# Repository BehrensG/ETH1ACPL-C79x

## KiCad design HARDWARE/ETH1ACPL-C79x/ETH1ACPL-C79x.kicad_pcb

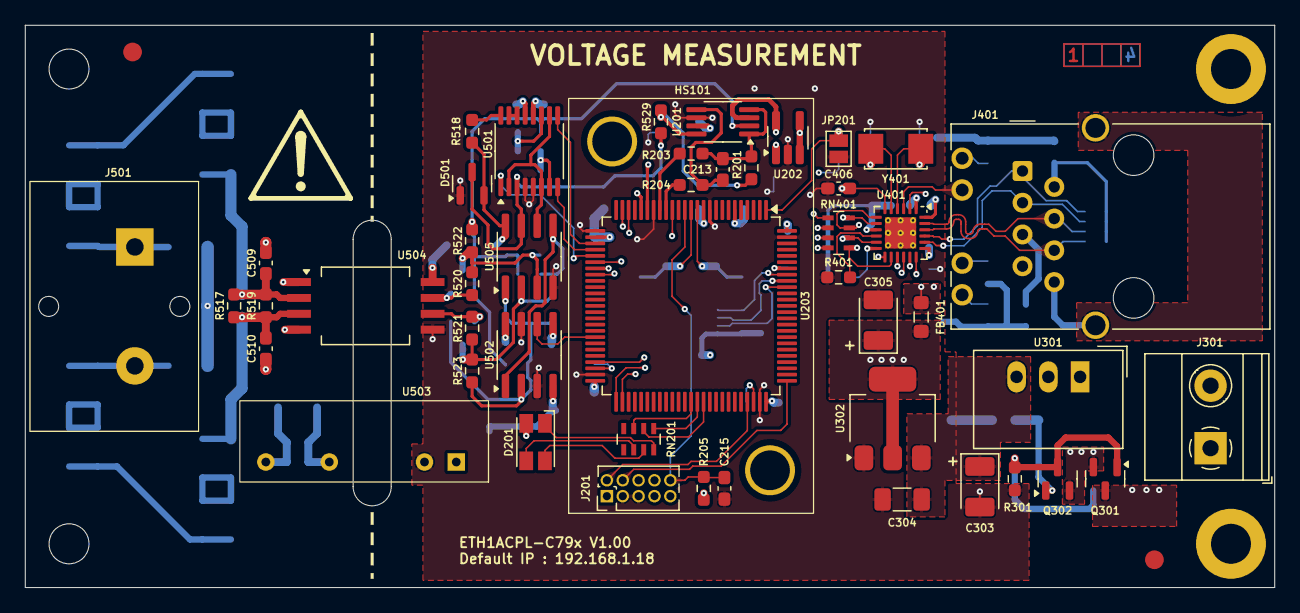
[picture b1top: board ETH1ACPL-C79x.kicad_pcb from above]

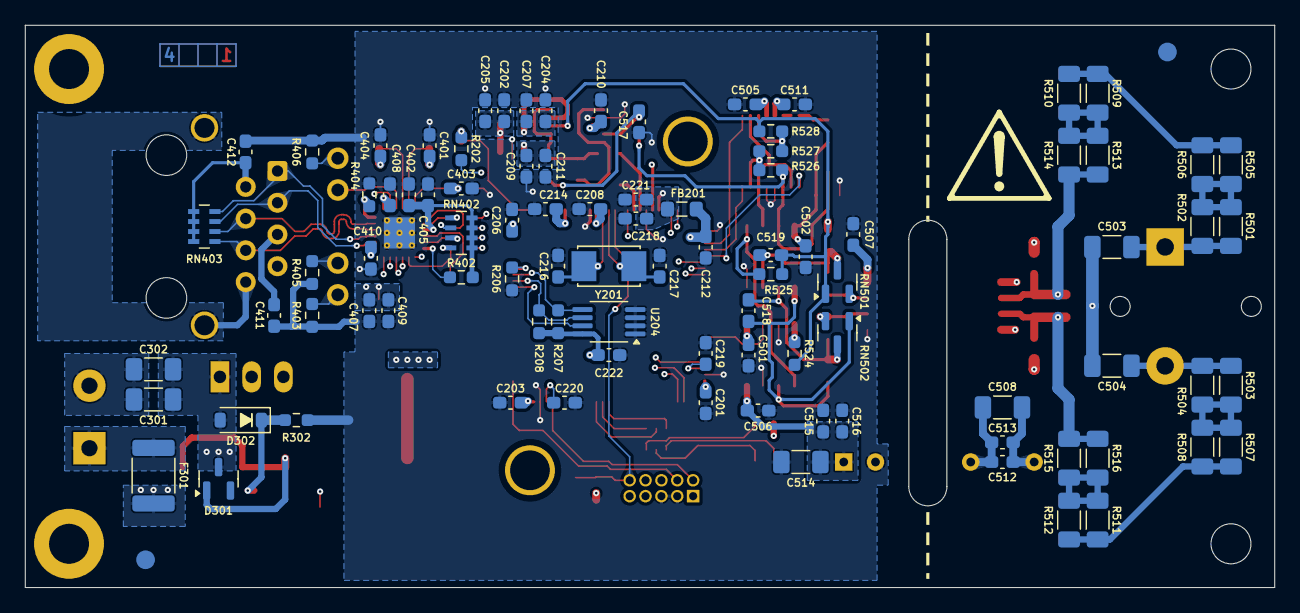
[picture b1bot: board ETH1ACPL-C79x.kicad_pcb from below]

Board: 4 copper layers, 100.0 x 45.0 mm, 148 parts (94 on the bottom side), 91 nets.

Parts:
C201, C203, C204, C205, C206, C208, C209, C210, C212, C215, C221, C222, C402, C408, C409, C410, C411, C412, C501, C502, C505, C506, C507, C511, C513, C516: 0.1u; C_0603_1608Metric_Pad1.08x0.95mm_HandSolder
C202, C207, C211, C214, C218, C405, C406, C407, C512, C515: 1u; C_0603_1608Metric_Pad1.08x0.95mm_HandSolder
C213: DNP; C_0603_1608Metric_Pad1.08x0.95mm_HandSolder
C216, C217, C401, C404: 8p; C_0603_1608Metric_Pad1.08x0.95mm_HandSolder
C219, C220: 2u2; C_0603_1608Metric_Pad1.08x0.95mm_HandSolder
C301: 10u/50V; C_1206_3216Metric_Pad1.33x1.80mm_HandSolder
C302: 4u7/50V; C_1206_3216Metric_Pad1.33x1.80mm_HandSolder
C303, C305: 22u; CP_EIA-3528-21_Kemet-B_Pad1.50x2.35mm_HandSolder
C304, C508, C514: 10u; C_1206_3216Metric_Pad1.33x1.80mm_HandSolder
C403: 470p; C_0603_1608Metric_Pad1.08x0.95mm_HandSolder
C503, C504: 1n/2kV; C_1206_3216Metric_Pad1.33x1.80mm_HandSolder
C509, C510: 470n/100; C_0603_1608Metric_Pad1.08x0.95mm_HandSolder
C517: 100p; C_0603_1608Metric_Pad1.08x0.95mm_HandSolder
C518, C519: 68p; C_0603_1608Metric_Pad1.08x0.95mm_HandSolder
D201: ASMB-MTB1-0B3A2; LED_Avago_PLCC4_3.2x2.8mm_CW
D301: BZX84C10LT1G; SOT-23
D302: 1N4148W; D_SOD-123
D501: BAV99; SOT-23
F301: 1812L075/33DR; Fuse_1812_4532Metric_Pad1.30x3.40mm_HandSolder
FB201, FB401: 742792031; L_0805_2012Metric_Pad1.05x1.20mm_HandSolder
FID101, FID102, FID103, FID104: Fiducial; Fiducial_1.5mm_Mask3mm
H101, H103: M3; MountingHole_3.2mm_M3_DIN965
H102, H104: M3; MountingHole_3.2mm_M3_DIN965_Pad
HS101: 960-19-12-S-AB-0
J201: 20021111-00010T4LF; PinHeader_2x05_P1.27mm_Vertical
J301: 1715721; TerminalBlock_Phoenix_MKDS-1,5-2_1x02_P5.00mm_Horizontal
J401: RJ45_Wuerth_7499010121A; RJ45_Wuerth_7499010121A_Horizontal
J501: 1710072
JP201: Open; SolderJumper-2_P1.3mm_Open_Pad1.0x1.5mm
Q301: SI5618A; SOT-23
Q302: MMBT3904; SOT-23
R201, R203, R204, R206, R524, R529: 0; R_0603_1608Metric_Pad0.98x0.95mm_HandSolder
R202, R205, R401, R403: 10k; R_0603_1608Metric_Pad0.98x0.95mm_HandSolder
R207, R208: 4k7; R_0603_1608Metric_Pad0.98x0.95mm_HandSolder
R301, R302, R518: 100k; R_0603_1608Metric_Pad0.98x0.95mm_HandSolder
R402: 1k5; R_0603_1608Metric_Pad0.98x0.95mm_HandSolder
R404: 12k1; R_0603_1608Metric_Pad0.98x0.95mm_HandSolder
R405, R406: 560; R_0603_1608Metric_Pad0.98x0.95mm_HandSolder
R501, R502, R503, R504, R505, R506, R507, R508, R509, R510, R511, R512, R513, R514, R515, R516: 56k; R_1206_3216Metric_Pad1.30x1.75mm_HandSolder
R517: 56; R_0603_1608Metric_Pad0.98x0.95mm_HandSolder
R519: 220; R_0603_1608Metric_Pad0.98x0.95mm_HandSolder
R520, R521: 10k/0.1%; R_0603_1608Metric_Pad0.98x0.95mm_HandSolder
R522, R523: 6k2/0.1%; R_0603_1608Metric_Pad0.98x0.95mm_HandSolder
R525: 100k/0.1%; R_0603_1608Metric_Pad0.98x0.95mm_HandSolder
R526: 180k/0.05%; R_0603_1608Metric_Pad0.98x0.95mm_HandSolder
R527: 18k/0.05%; R_0603_1608Metric_Pad0.98x0.95mm_HandSolder
R528: 2k/0.05%; R_0603_1608Metric_Pad0.98x0.95mm_HandSolder
RN201: EXB-V8V102JV; R_Array_Concave_4x0603
RN401: EXB-V8V330JV; R_Array_Concave_4x0603
RN402: EXB-V8V103JV; R_Array_Concave_4x0603
RN403: EXB-38V510JV; R_Array_Concave_4x0603
RN501, RN502: MPMT50011002AT5; SOT-23
SYM501, SYM502: SYM_Flash_Small; Symbol_Attention_Triangle_8x7mm_Copper
U201: LT6350xMS8; MSOP-8_3x3mm_P0.65mm
U202: REF1933AIDDCT; SOT-23-5_HandSoldering
U203: STM32H743VITx; LQFP-100_14x14mm_P0.5mm
U204: 24LC08B-E/MS; MSOP-8_3x3mm_P0.65mm
U301: TSR_1-2450; Converter_DCDC_TRACO_TSR-1_THT
U302: LM1117MP-3.3/NOPB; SOT-223-3_TabPin2
U401: LAN8742A; VQFN-24-1EP_4x4mm_P0.5mm_EP2.5x2.5mm_ThermalVias
U501: DG412LEDQ; TSSOP-16_4.4x5mm_P0.65mm
U502: DG419LEDY; SOIC-8_3.9x4.9mm_P1.27mm
U503: TBA 1-0511HI; TBA1
U504: ACPL-C79B; SSO-8_6.8x5.9mm_P1.27mm_Clearance8mm
U505: OPA2340UA; SOIC-8_3.9x4.9mm_P1.27mm
Y201: NX5032GA-16; NX5032GA
Y401: NX5032GA-25; NX5032GA

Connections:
+1.65V: C209.1, C211.1, C519.2, R522.1, R524.2, R525.2, R528.2, RN501.1, U201.2 (+IN2), U202.1 (Vbias)
+3.3V: C201.1, C203.1, C206.1, C208.1, C212.1, C214.1, C222.2, C305.1, C402.1, C405.1, C501.1, C502.1, C505.1, D201.4 (A), D501.2 (A), FB201.2, FB401.2, J201.1, R202.2, R205.1, R207.1, R208.1, R402.1, R518.2, RN402.5 (R4.2), RN402.6 (R3.2), RN402.7 (R2.2), RN402.8 (R1.2), U203.6 (VBAT), U203.11 (VDD), U203.27 (VDD), U203.50 (VDD), U203.75 (VDD), U203.100 (VDD), U204.8 (VCC), U302.2 (VO), U401.9 (VDDIO), U501.12 (VL), U502.5 (VL), U505.8 (V+)
+3.3VADC: C204.1, C207.1, C210.1, U201.3 (V+), U201.7 (~SHDN), U202.5 (Vref), U203.20 (VREF+)
+5V: C202.1, C205.1, C303.1, C304.1, C506.1, C507.1, C511.1, C514.1, C515.1, C516.1, U202.3 (EN), U202.4 (Vin), U301.3 (Vout), U302.3 (VI), U501.13 (V+), U502.4 (V+), U503.1 (+Vin), U504.8 (VDD2)
+5VP: C508.1, C512.1, C513.1, U503.6 (+Vout), U504.1 (VDD1)
/Ethernet/ETH_RXN: J401.6 (RD-), RN403.1 (R1.1), U401.22 (RXN)
/Ethernet/ETH_RXP: J401.4 (RD+), RN403.2 (R2.1), U401.23 (RXP)
/Ethernet/ETH_TXN: J401.3 (TD-), RN403.3 (R3.1), U401.20 (TXN)
/Ethernet/ETH_TXP: J401.1 (TD+), RN403.4 (R4.1), U401.21 (TXP)
/Ethernet/LED1: J401.10, U401.3 (LED1/REGOFF)
/Ethernet/LED2: J401.12, R403.1, U401.2 (LED2/~INTSEL)
/Ethernet/MODE0: RN401.8 (R1.2), RN402.1 (R1.1), U401.8 (RXD0/MODE0)
/Ethernet/MODE1: RN401.7 (R2.2), RN402.2 (R2.1), U401.7 (RXD1/MODE1)
/Ethernet/MODE2: RN401.6 (R3.2), RN402.3 (R3.1), U401.11 (CRS_DV/MODE2)
/Ethernet/REFCLK0: RN401.5 (R4.2), RN402.4 (R4.1), U401.14 (~INT/REFCLKO)
/Ethernet/REF_CLK: RN401.4 (R4.1), U203.23 (PA1)
/Ethernet/RMII_CRS_DV: RN401.3 (R3.1), U203.31 (PA7)
/Ethernet/RMII_MDC: U203.16 (PC1), U401.13 (MDC)
/Ethernet/RMII_MDIO: R402.2, U203.24 (PA2), U401.12 (MDIO)
/Ethernet/RMII_RXD0: RN401.1 (R1.1), U203.32 (PC4)
/Ethernet/RMII_RXD1: RN401.2 (R2.1), U203.33 (PC5)
/Ethernet/RMII_TXD0: U203.51 (PB12), U401.17 (TXD0)
/Ethernet/RMII_TXD1: U203.52 (PB13), U401.18 (TXD1)
/Ethernet/RMII_TXEN: U203.47 (PB11), U401.16 (TXEN)
/MCU/EEPROM_WP: U203.91 (PB5), U204.7 (WP)
/MCU/I2C1_SCL: R208.2, U203.92 (PB6), U204.6 (SCL)
/MCU/I2C1_SDA: R207.2, U203.93 (PB7), U204.5 (SDA)
/MCU/LED_BLUE: RN201.3 (R3.1), U203.63 (PC6)
/MCU/LED_GREEN: RN201.2 (R2.1), U203.65 (PC8)
/MCU/LED_RED: RN201.1 (R1.1), U203.64 (PC7)
/MCU/MCU_DEF: JP201.1 (A), R202.1, U203.1 (PE2)
/MCU/MCU_G1: U203.30 (PA6), U501.1
/MCU/MCU_G10: U203.29 (PA5), U501.8
/MCU/MCU_G100: U203.28 (PA4), U501.9
/MCU/MCU_ZOFFS: U203.43 (PE13), U502.6
/MCU/NRST: C215.1, J201.10, R205.2, U203.14 (NRST), U401.15 (~RST)
/MCU/TCK_SWCLK: J201.4, U203.76 (PA14)
/MCU/TMS_SWDIO: J201.2, U203.72 (PA13)
/MCU/VOUT: C517.1, R201.1, R529.2, U201.8 (+IN1)
/MCU/VOUTN: R204.2, U203.17 (PC2_C)
/MCU/VOUTP: R203.2, U203.18 (PC3_C)
Earth: J401.8, J401.SH
GND: C201.2, C202.2, C203.2, C204.2, C205.2, C206.2, C207.2, C208.2, C209.2, C210.2, C211.2, C212.2, C214.2, C215.2, C216.2, C217.2, C218.2, C219.2, C220.2, C221.2, C222.1, C301.2, C302.2, C303.2, C304.2, C305.2, C401.2, C402.2, C403.2, C404.2, C405.2, C406.2, C407.2, C408.2, C409.2, C410.2, C411.2, C412.2, C501.2, C502.2, C505.2, C506.2, C507.2, C511.2, C514.2, C515.2, C516.2, C517.2, D501.1 (K), J201.3, J201.5, J301.2, JP201.2 (B), R206.1, R301.2, R302.2, R401.1, R403.2, R404.1, R405.2, R406.2, U201.6 (V-), U202.2 (GND), U203.10 (VSS), U203.19 (VSSA), U203.26 (VSS), U203.49 (VSS), U203.74 (VSS), U203.99 (VSS), U204.1 (A0), U204.2 (A1), U204.3 (A2), U204.4 (GND), U301.2 (GND), U302.1 (GND), U401.25 (VSS), U501.4 (V-), U501.5 (GND), U502.3 (GND), U502.7 (V-), U503.2 (-Vin), U504.5 (GND2), U505.4 (V-)
GND1: C503.2, C504.1, C508.2, C509.2, C510.1, C512.2, C513.2, U503.4 (-Vout), U504.4 (GND1)
unnamed: C219.1, U203.48 (VCAP)
unnamed: C220.1, U203.73 (VCAP)
unnamed: C518.2, R523.2, RN502.1, U502.2, U505.1
unnamed: D201.3 (BK), RN201.6 (R3.2)
unnamed: D201.2 (GK), RN201.7 (R2.2)
unnamed: D201.1 (RK), RN201.8 (R1.2)
unnamed: D301.1 (A), Q301.1 (G), Q302.3 (C), R301.1
unnamed: C301.1, C302.1, D301.3 (K), D302.2 (A), Q301.2 (S), Q302.2 (E), U301.1 (Vin)
unnamed: D302.1 (K), Q302.1 (B), R302.1
unnamed: D501.3 (K), R526.1, R529.1, U501.3, U505.7
unnamed: F301.1, J301.1
unnamed: J401.9, R406.1
unnamed: J401.11, R405.1
unnamed: C503.1, J501.1, R501.1, R502.1
unnamed: C504.2, J501.2, R503.1, R504.1
unnamed: F301.2, Q301.3 (D)
unnamed: R501.2, R502.2, R505.1, R506.1
unnamed: R503.2, R504.2, R507.1, R508.1
unnamed: R505.2, R506.2, R509.1, R510.1
unnamed: R507.2, R508.2, R511.1, R512.1
unnamed: R509.2, R510.2, R513.1, R514.1
unnamed: R511.2, R512.2, R515.1, R516.1
unnamed: R518.1, U501.16
unnamed: R524.1, U502.8
unnamed: R526.2, R527.1, U501.7
unnamed: R527.2, R528.1, U501.11
unnamed: C213.1, R201.2, R203.1, U201.1 (-IN1), U201.4 (OUT1)
unnamed: C213.2, R204.1, U201.5 (OUT2)
unnamed: R206.2, U203.94 (BOOT0)
unnamed: C216.1, U203.12 (PH0), Y201.1
unnamed: C217.1, U203.13 (PH1), Y201.2
unnamed: R404.2, U401.24 (RBIAS)
unnamed: R401.2, U401.10 (RXER/PHYAD0)
unnamed: C403.1, C406.1, U401.6 (VDDCR)
unnamed: C401.1, U401.5 (XTAL1/CLKIN), Y401.2
unnamed: C404.1, U401.4 (XTAL2), Y401.1
unnamed: U501.14, U501.15
unnamed: C509.1, R513.2, R514.2, R517.1, R519.1, U504.2 (IN+)
unnamed: C510.2, R515.2, R516.2, R517.2, R519.2, U504.3 (IN-)
unnamed: R520.1, RN501.2, U504.7 (OUT+)
unnamed: R521.1, RN502.2, U504.6 (OUT-)
unnamed: C519.1, R520.2, R522.2, RN501.3, U505.3 (+)
unnamed: C518.1, R521.2, R523.1, RN502.3, U505.2 (-)
unnamed: R525.1, U502.1, U505.5 (+)
unnamed: U501.2, U501.6, U501.10, U505.6 (-)
VCCQ: C407.1, C408.1, C409.1, C410.1, C411.1, C412.1, FB401.1, J401.2 (TCT), J401.5 (RCT), RN403.5 (R4.2), RN403.6 (R3.2), RN403.7 (R2.2), RN403.8 (R1.2), U401.1 (VDD2A), U401.19 (VDD1A)
VDDA: C218.1, C221.1, FB201.1, U203.21 (VDDA)

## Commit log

2024-03-22 Development
2024-04-17 PCB design changes.
2024-04-22 Hardware design
